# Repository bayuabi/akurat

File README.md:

# AKURAT
AKURAT stands for "Alat Ukur Kadar Air Tanah", an IoT based soil moisture sensor with ESP-32 inside. This project dedicated for soil
moisture data logging and then collected data can be analyzed for research purpose.

### Specifications :
- Wi-Fi based IoT
- OLED Display
- Solar panel energy harvesting
- 3500 mAh Lithium Ion battery
- Deep sleep enabled (for long time battery life)

### Further Specifications :
- LoRa/NB-IoT IoT protocols

Reach me on email (bayuabi31@gmail.com) for more informations.

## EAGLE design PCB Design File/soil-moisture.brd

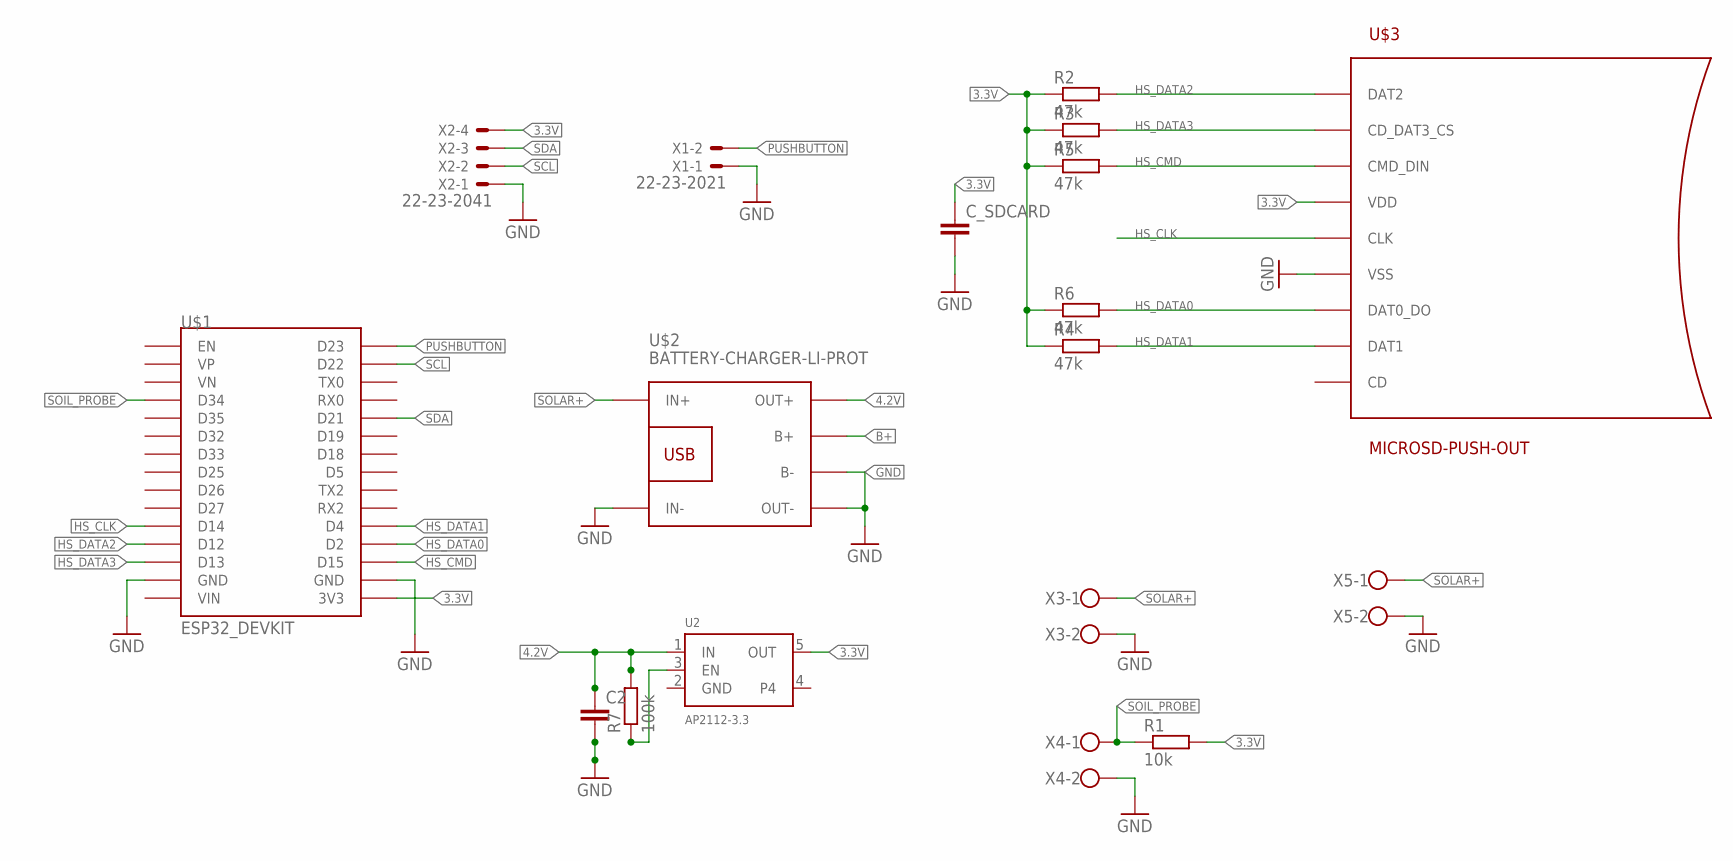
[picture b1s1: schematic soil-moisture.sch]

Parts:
C2: C-EUC0805; C0805
C_SDCARD: C-EUC0805; C0805
R1: 10k; R0805
R2, R3, R4, R5, R6: 47k; R0805
R7: 100k; R0805
U2: AP2112-3.3; SOT23-5
U$1: ESP32_DEVKIT
U$2: BATTERY-CHARGER-LI-PROT
U$3: MICROSD-PUSH-OUT
X1: 22-23-2021
X2: 22-23-2041
X3, X4, X5: W237-102

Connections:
3.3V: C_SDCARD.1, R1.2, R2.1, R3.1, R4.1, R5.1, R6.1, U2.5 (OUT), U$1.3V3, U$3.4 (VDD), X2.4
4.2V: C2.1, R7.2, U2.1 (IN), U$2.OUT+
B+: U$2.B+
GND: C2.2, C_SDCARD.2, U2.2 (GND), U$1.GND@1 (GND), U$1.GND@2 (GND), U$2.B-, U$2.IN-, U$2.OUT-, U$3.6 (VSS), U$3.G1 (VSS), U$3.G2 (VSS), U$3.G3 (VSS), U$3.G4 (VSS), X1.1, X2.1, X3.2, X4.2, X5.2
HS_CLK: U$1.D14, U$3.5 (CLK)
HS_CMD: R5.2, U$1.D15, U$3.3 (CMD_DIN)
HS_DATA0: R6.2, U$1.D2, U$3.7 (DAT0_DO)
HS_DATA1: R4.2, U$1.D4, U$3.8 (DAT1)
HS_DATA2: R2.2, U$1.D12, U$3.1 (DAT2)
HS_DATA3: R3.2, U$1.D13, U$3.2 (CD_DAT3_CS)
unnamed: R7.1, U2.3 (EN)
PUSHBUTTON: U$1.D23, X1.2
SCL: U$1.D22, X2.2
SDA: U$1.D21, X2.3
SOIL_PROBE: R1.1, U$1.D34, X4.1
SOLAR+: U$2.IN+, X3.1, X5.1

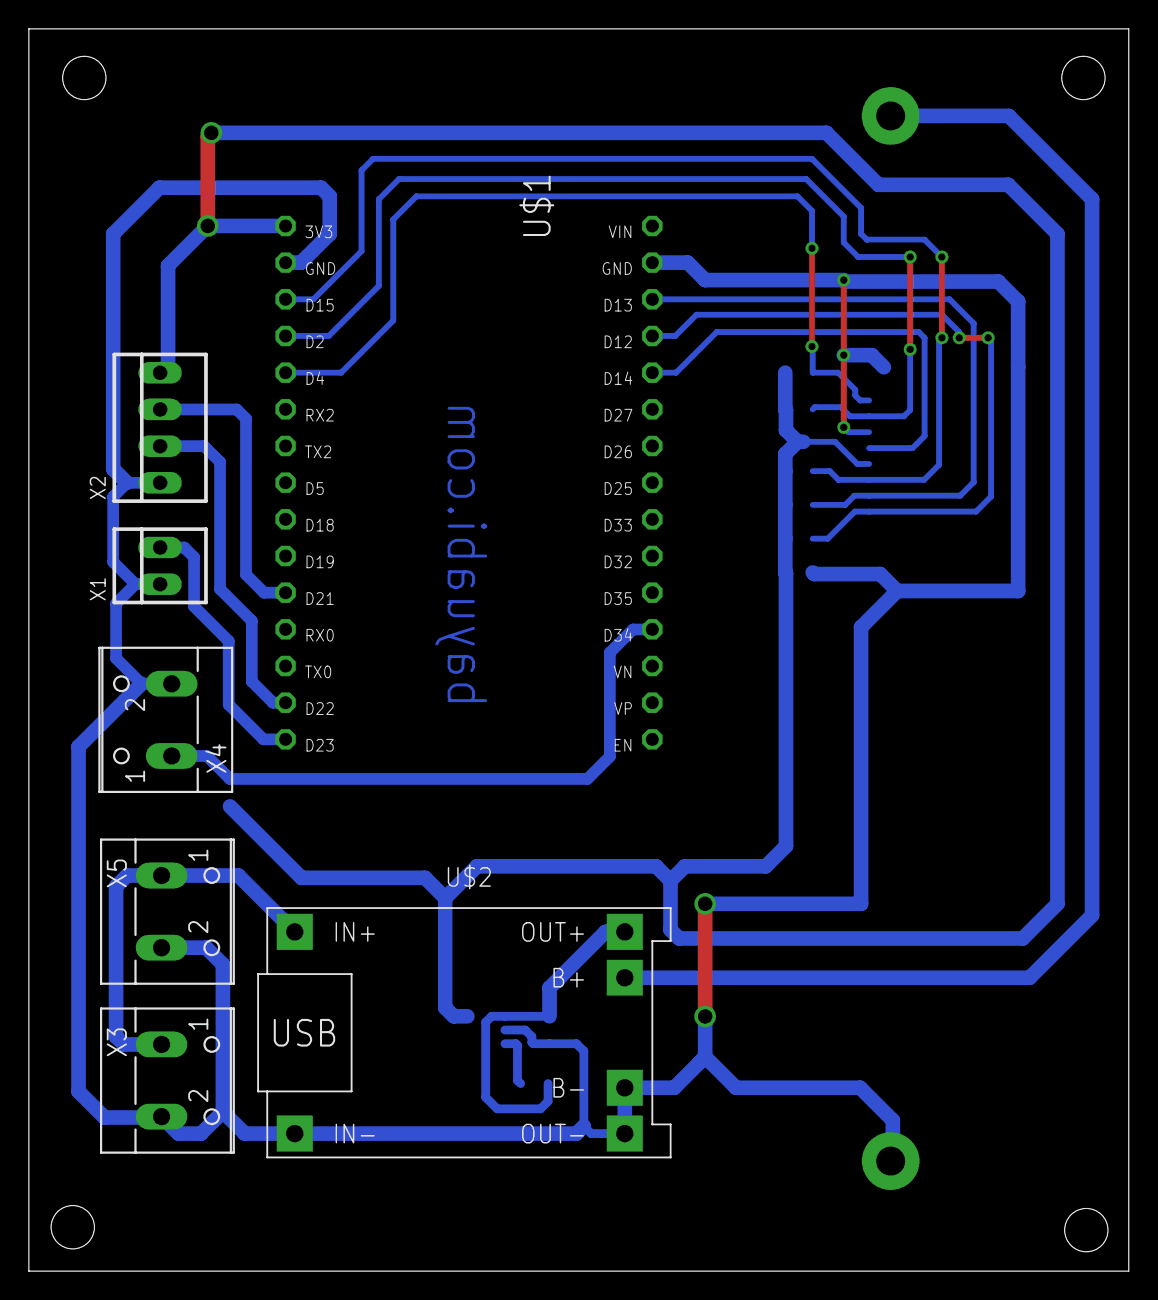
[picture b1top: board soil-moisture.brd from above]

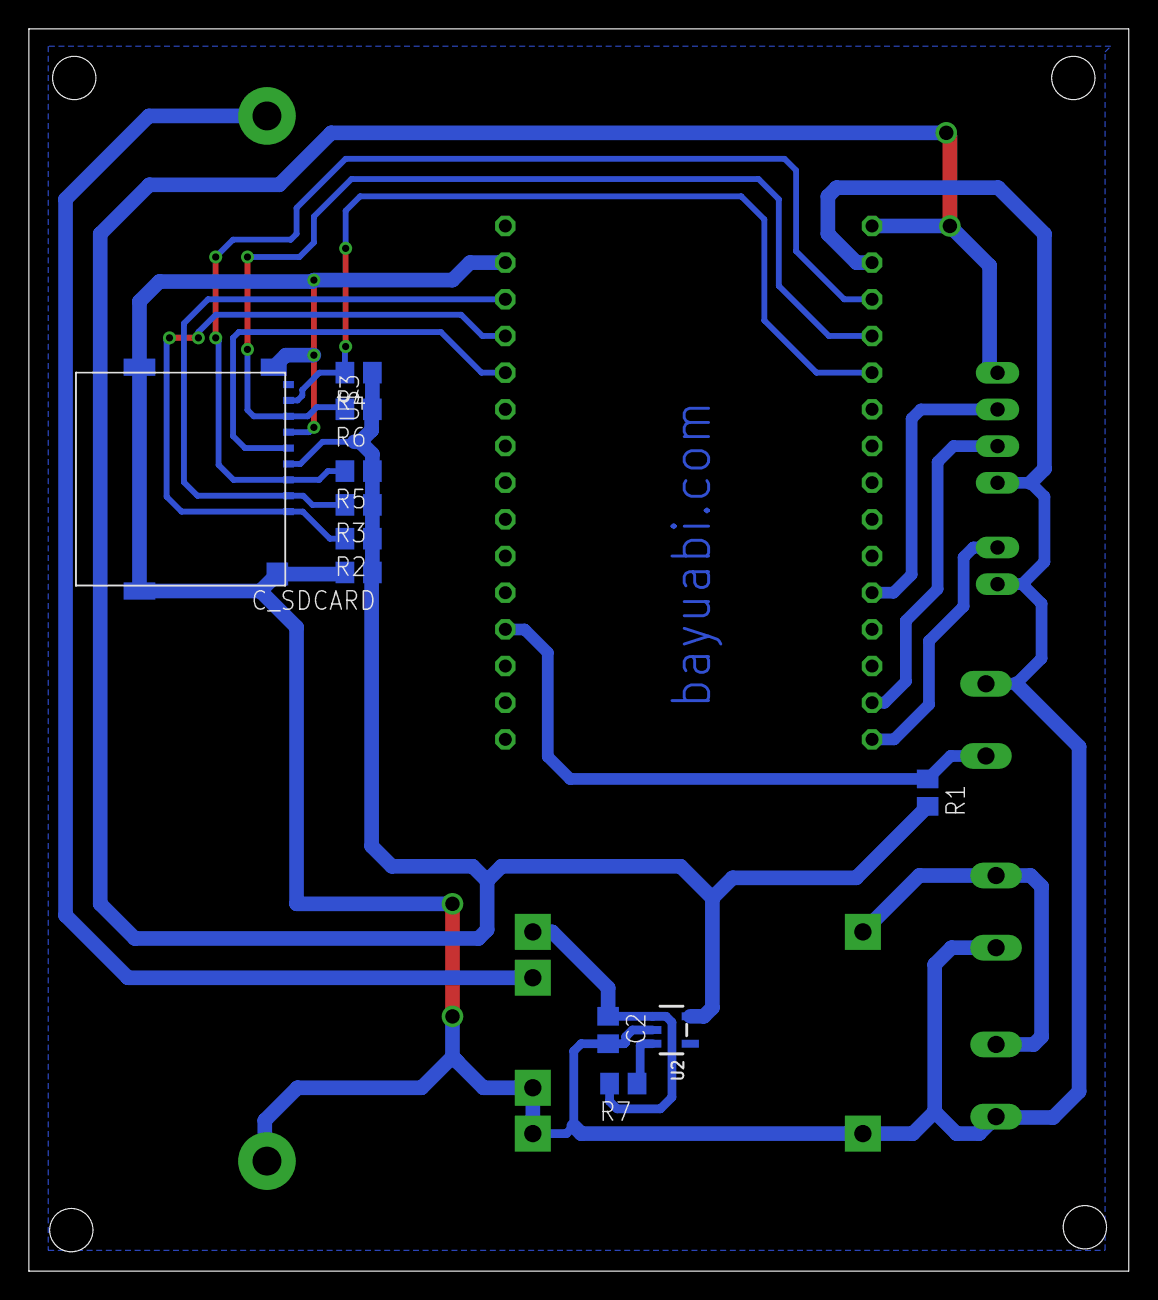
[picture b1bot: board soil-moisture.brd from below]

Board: 2 copper layers, 76.2 x 86.0 mm, 18 parts (11 on the bottom side), 15 nets.

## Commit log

2020-07-06 add pcb design file
2020-07-06 add new folder
2020-07-06 add esp-32 code file
2020-07-08 add board eagle 7
2020-07-11 wifi init etc done
2020-07-14 tambah perhitungan tegangan baterai

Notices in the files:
parts and their libraries:
diy-modules: Released under the Creative Commons Attribution 4.0 International License: http://creativecommons.org/licenses/by/4.0
microbuilder: This work is placed in the public domain, and may be freely used for commercial and non-commercial work with the following conditions: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
